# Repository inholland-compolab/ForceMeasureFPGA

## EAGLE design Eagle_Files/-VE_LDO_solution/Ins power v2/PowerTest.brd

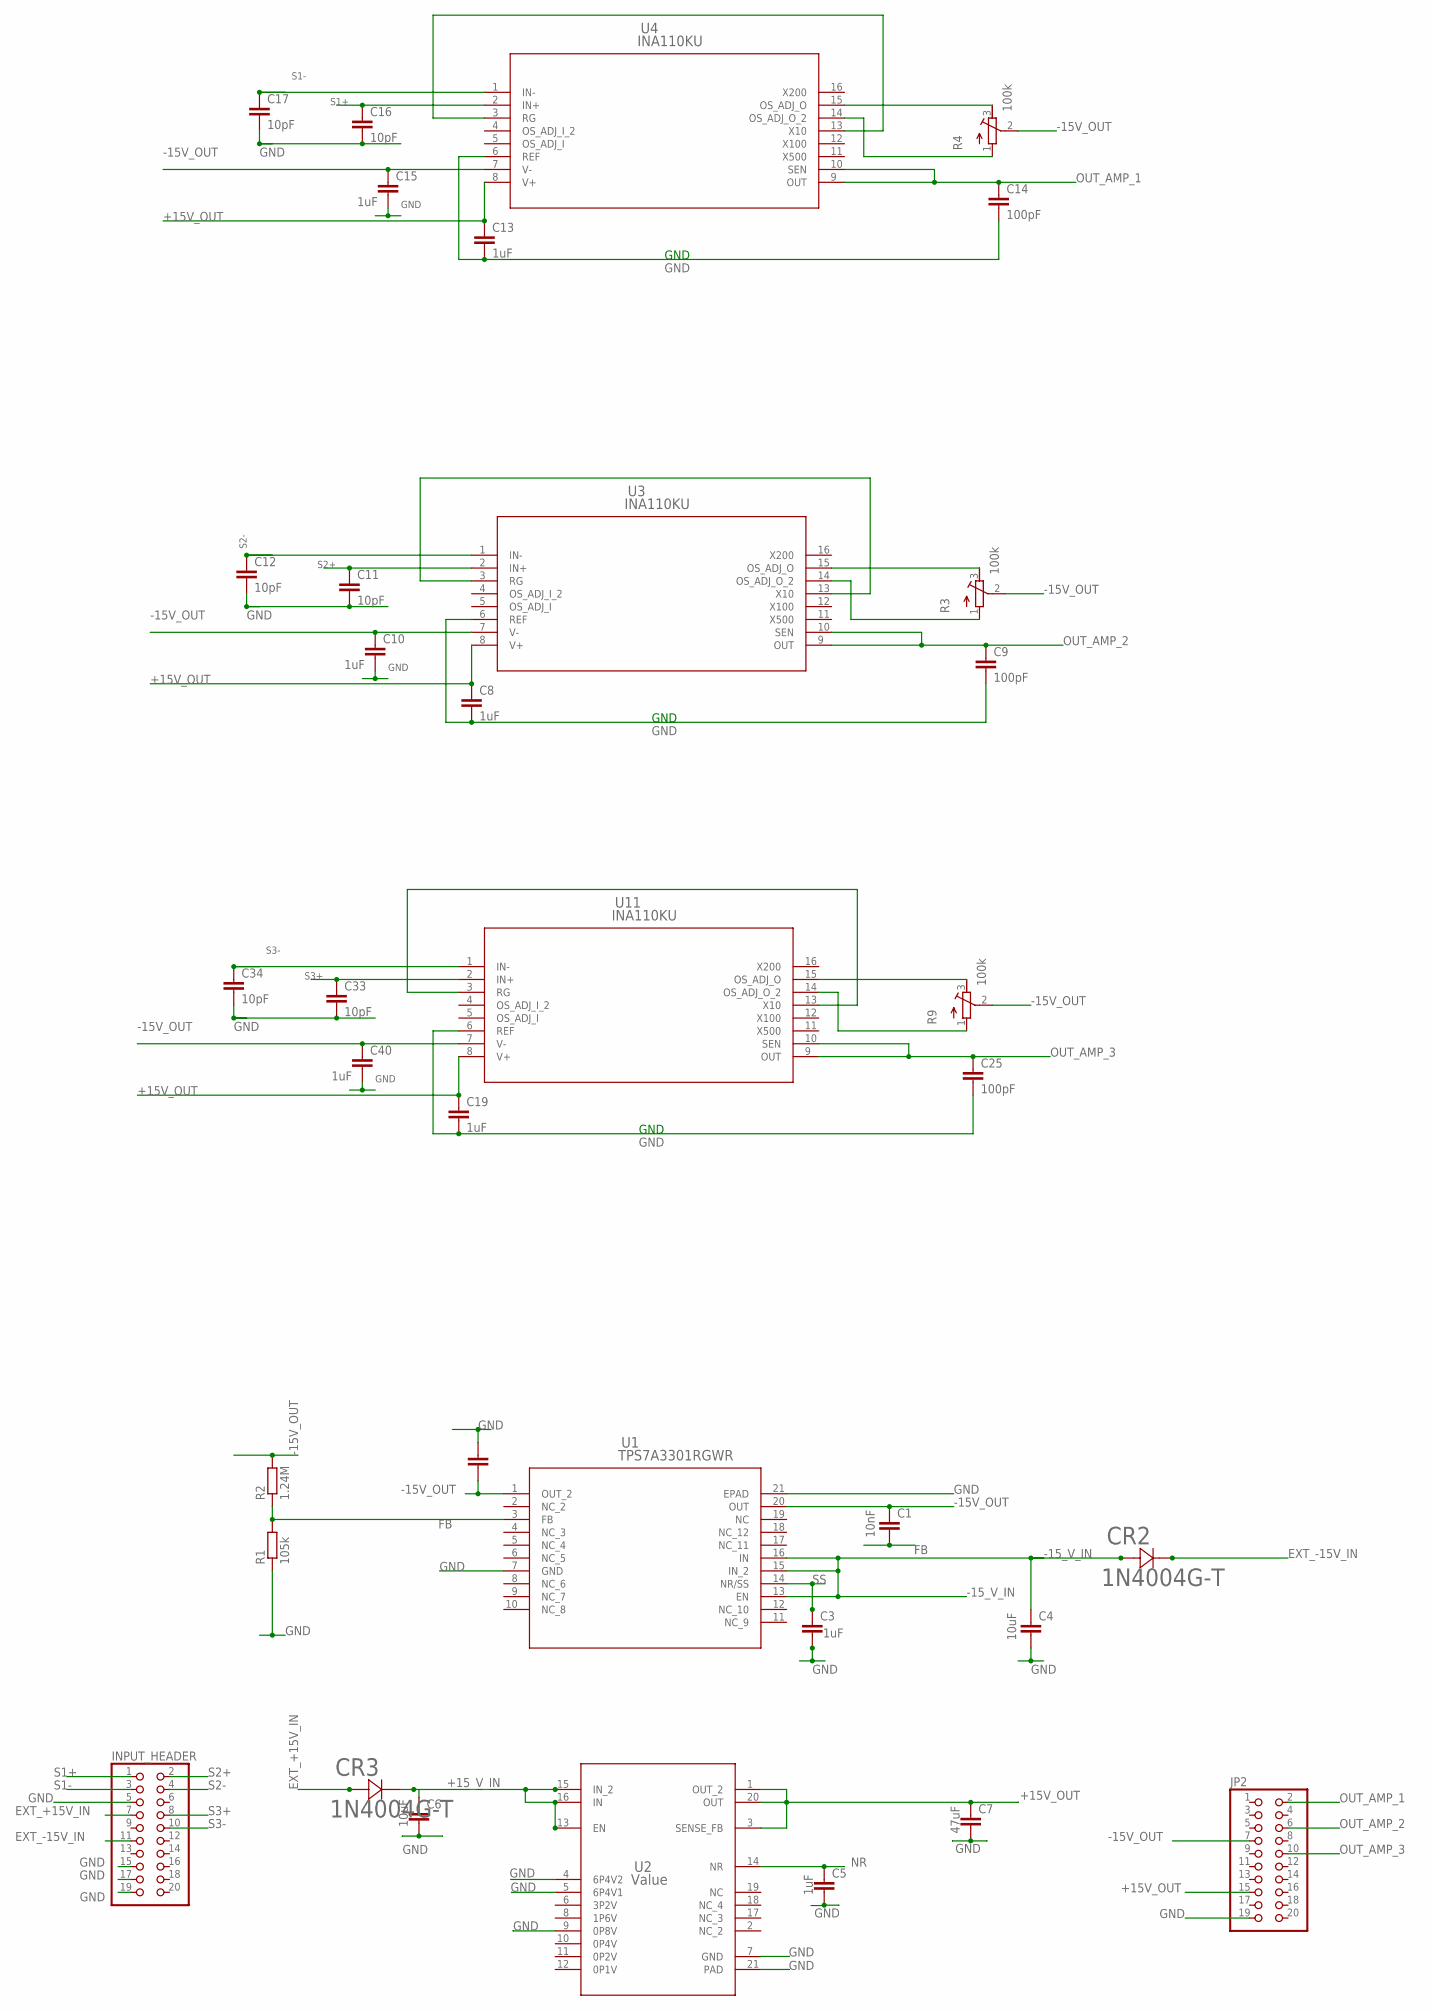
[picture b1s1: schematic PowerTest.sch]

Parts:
C1: 10nF; C1210
C3, C5, C8, C10, C13, C15, C19, C40: 1uF; C1210
C4, C6: 10uF; C1210
C7, C55: 47uF; C1210
C9, C14, C25: 100pF; C1210
C11, C12, C16, C17, C33, C34: 10pF; C1210
CR2, CR3: 1N4004G-T; DO-41
INPUT_HEADER: PINHD-2X10; 2X10
JP2: PINHD-2X10; 2X10
R1: 105k; RESC2012X65
R2: 1.24M; RESC2012X65
R3, R4, R9: 100k; RTRIM3296Y
U1: TPS7A3301RGWR; RGW0020A
U2: Value; RGW0020A
U3, U4, U11: INA110KU; SO-G16G6.9

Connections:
+15V_OUT: C7.1, C8.1, C13.1, C19.1, JP2.15, U2.1 (OUT_2), U2.3 (SENSE_FB), U2.20 (OUT), U3.8 (V+), U4.8 (V+), U11.8 (V+)
+15_V_IN: C6.1, CR3.1, U2.13 (EN), U2.15 (IN_2), U2.16 (IN)
-15V_OUT: C1.1, C10.1, C15.1, C40.1, C55.2, JP2.7, R2.2, R3.2 (S), R4.2 (S), R9.2 (S), U1.1 (OUT_2), U1.20 (OUT), U3.7 (V-), U4.7 (V-), U11.7 (V-)
-15_V_IN: C4.1, CR2.2, U1.13 (EN), U1.15 (IN_2), U1.16 (IN)
EXT_+15V_IN: CR3.2, INPUT_HEADER.7
EXT_-15V_IN: CR2.1, INPUT_HEADER.11
FB: C1.2, R1.2, R2.1, U1.3 (FB)
GND: C3.2, C4.2, C5.2, C6.2, C7.2, C8.2, C9.2, C10.2, C11.2, C12.2, C13.2, C14.2, C15.2, C16.2, C17.2, C19.2, C25.2, C33.2, C34.2, C40.2, C55.1, INPUT_HEADER.5, INPUT_HEADER.15, INPUT_HEADER.17, INPUT_HEADER.19, JP2.19, R1.1, U1.7 (GND), U1.21 (EPAD), U2.4 (6P4V2), U2.5 (6P4V1), U2.7 (GND), U2.9 (0P8V), U2.21 (PAD), U3.6 (REF), U4.6 (REF), U11.6 (REF)
unnamed: U3.3 (RG), U3.13 (X10)
unnamed: U11.3 (RG), U11.13 (X10)
unnamed: R3.3 (E), U3.15 (OS_ADJ_O)
unnamed: R3.1 (A), U3.14 (OS_ADJ_O_2)
unnamed: U4.3 (RG), U4.13 (X10)
unnamed: R4.3 (E), U4.15 (OS_ADJ_O)
unnamed: R4.1 (A), U4.14 (OS_ADJ_O_2)
unnamed: R9.3 (E), U11.15 (OS_ADJ_O)
unnamed: R9.1 (A), U11.14 (OS_ADJ_O_2)
NR: C5.1, U2.14 (NR)
OUT_AMP_1: C14.1, JP2.2, U4.9 (OUT), U4.10 (SEN)
OUT_AMP_2: C9.1, JP2.6, U3.9 (OUT), U3.10 (SEN)
OUT_AMP_3: C25.1, JP2.10, U11.9 (OUT), U11.10 (SEN)
S1+: C16.1, INPUT_HEADER.1, U4.2 (IN+)
S1-: C17.1, INPUT_HEADER.3, U4.1 (IN-)
S2+: C11.1, INPUT_HEADER.2, U3.2 (IN+)
S2-: C12.1, INPUT_HEADER.4, U3.1 (IN-)
S3+: C33.1, INPUT_HEADER.8, U11.2 (IN+)
S3-: C34.1, INPUT_HEADER.10, U11.1 (IN-)
SS: C3.1, U1.14 (NR/SS)

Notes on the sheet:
GND

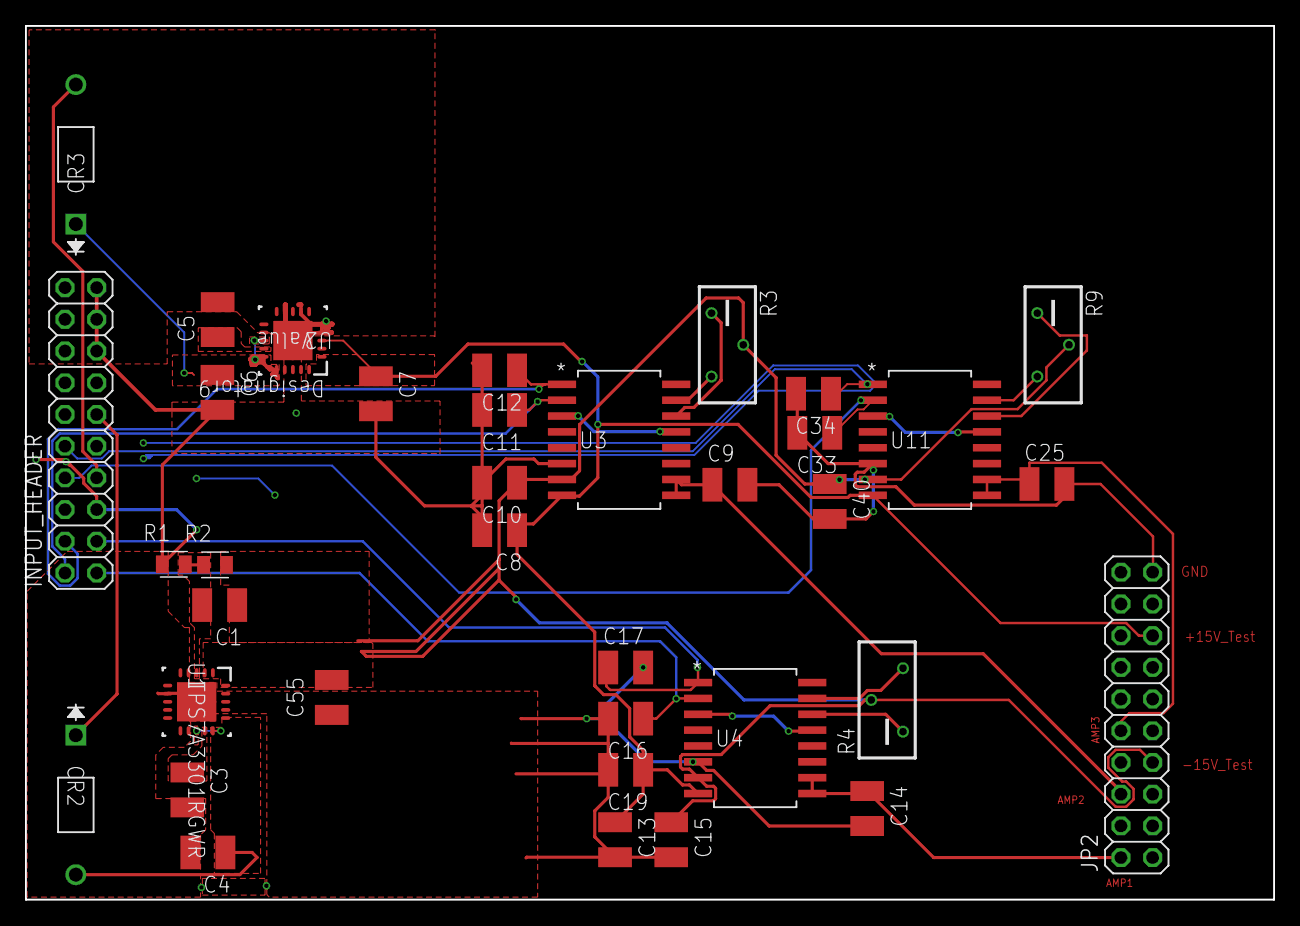
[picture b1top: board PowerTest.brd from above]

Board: 2 copper layers, 100.0 x 70.0 mm, 36 parts (0 on the bottom side), 28 nets.

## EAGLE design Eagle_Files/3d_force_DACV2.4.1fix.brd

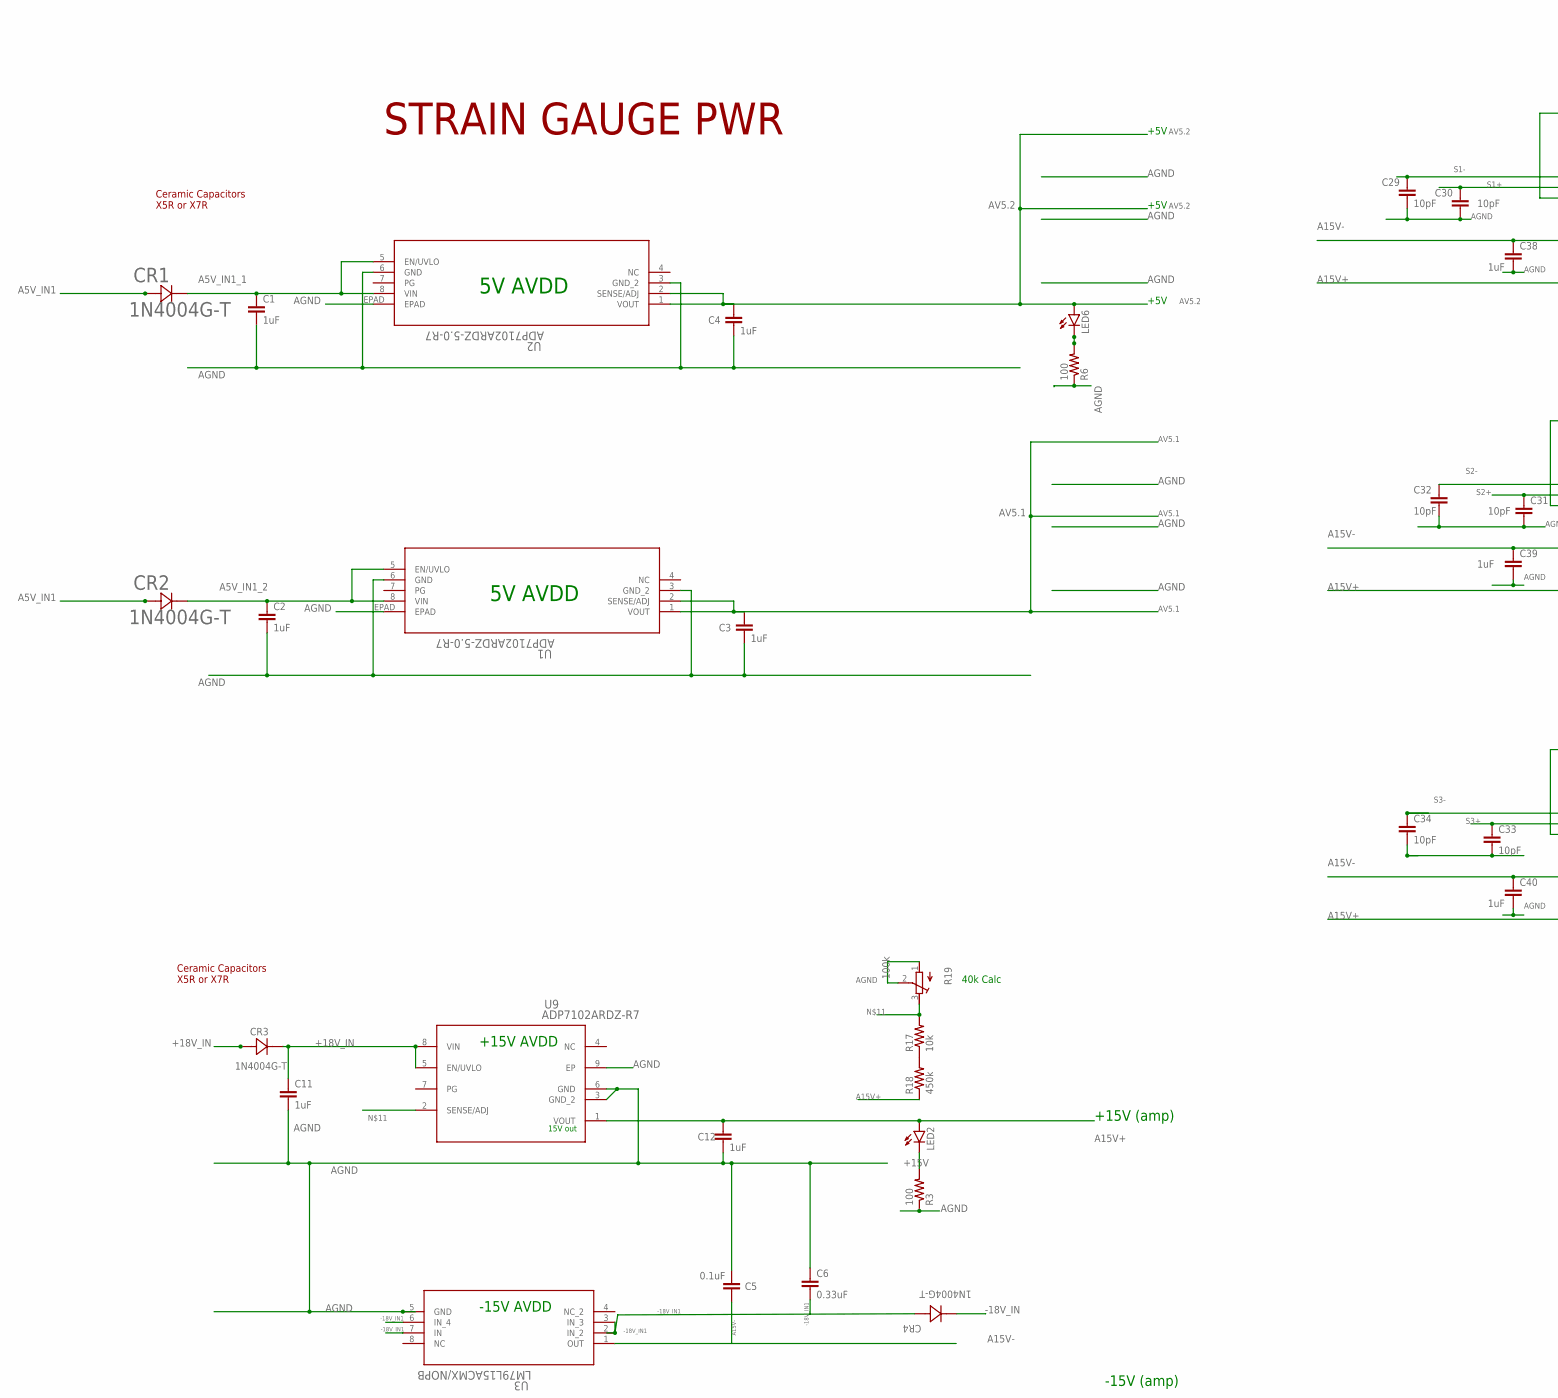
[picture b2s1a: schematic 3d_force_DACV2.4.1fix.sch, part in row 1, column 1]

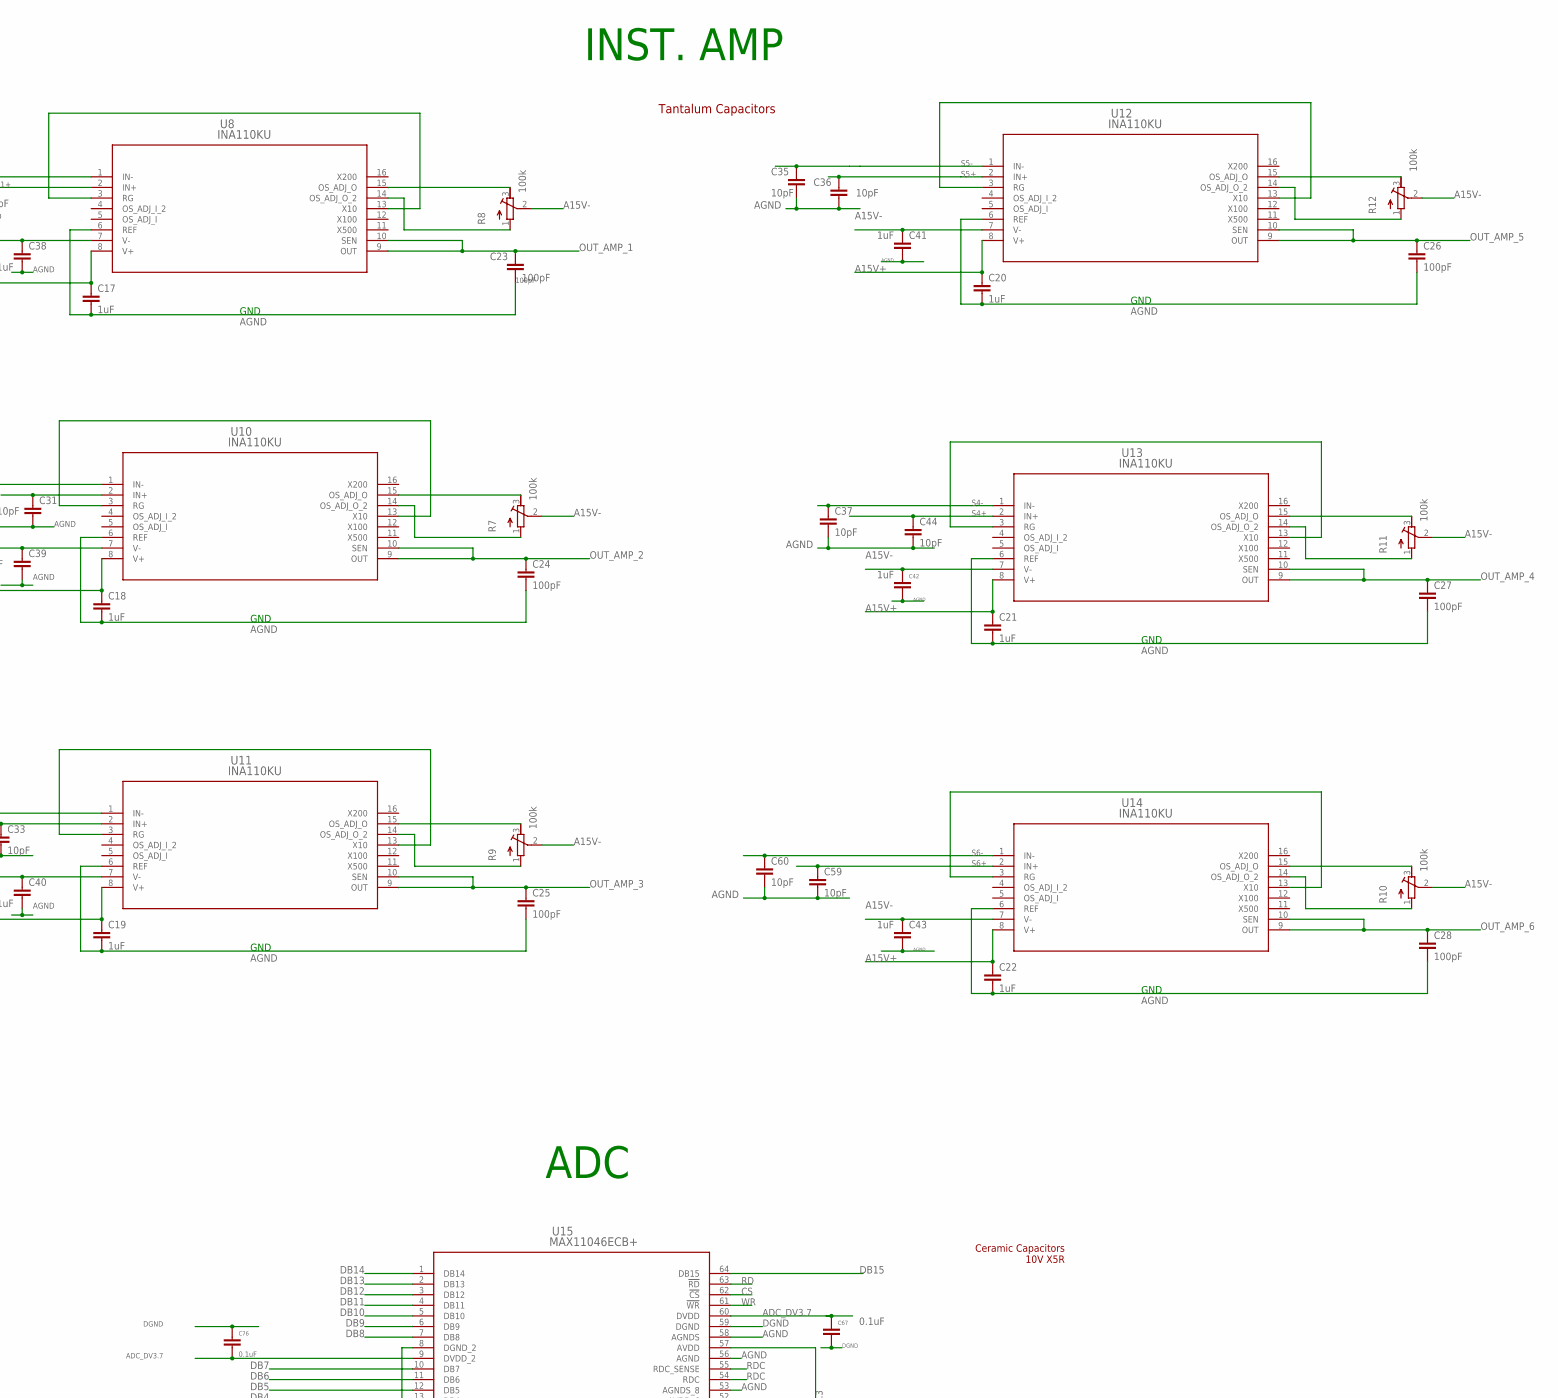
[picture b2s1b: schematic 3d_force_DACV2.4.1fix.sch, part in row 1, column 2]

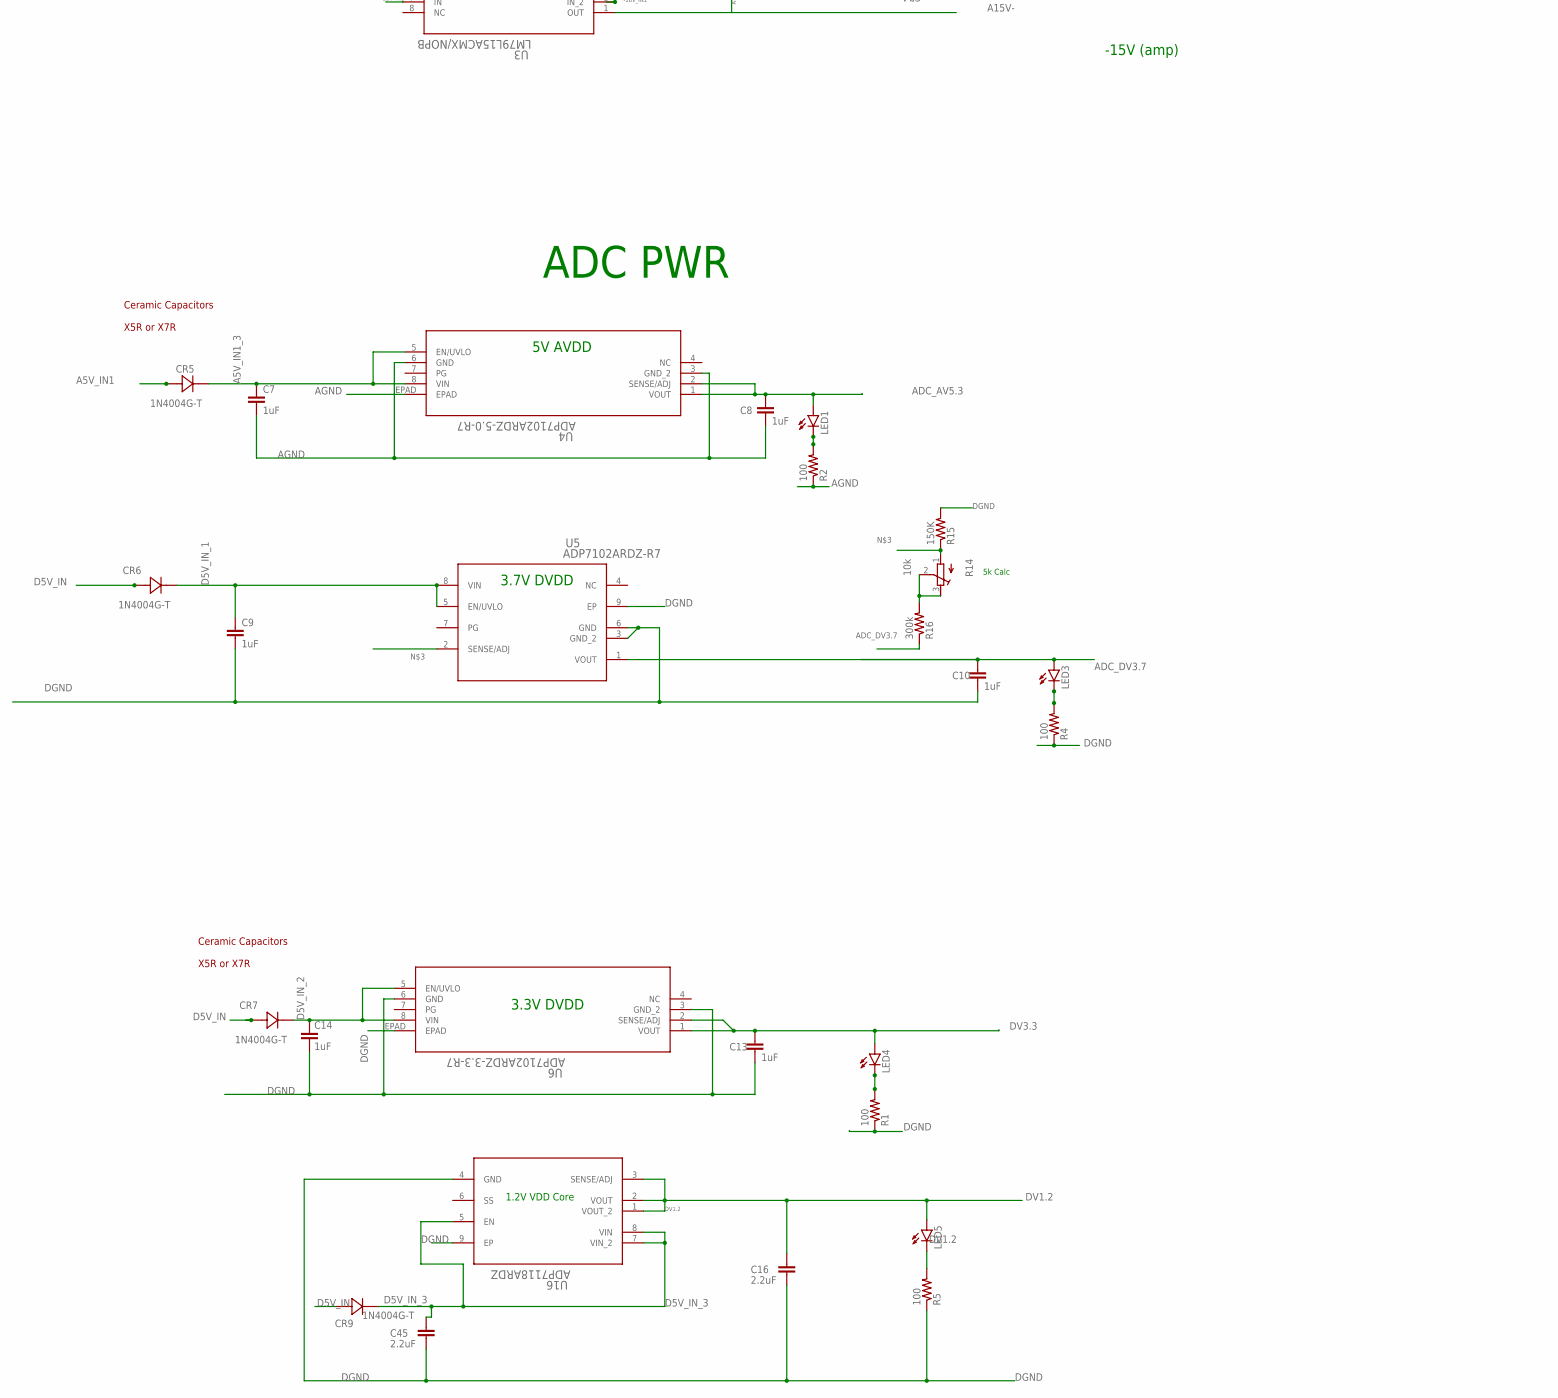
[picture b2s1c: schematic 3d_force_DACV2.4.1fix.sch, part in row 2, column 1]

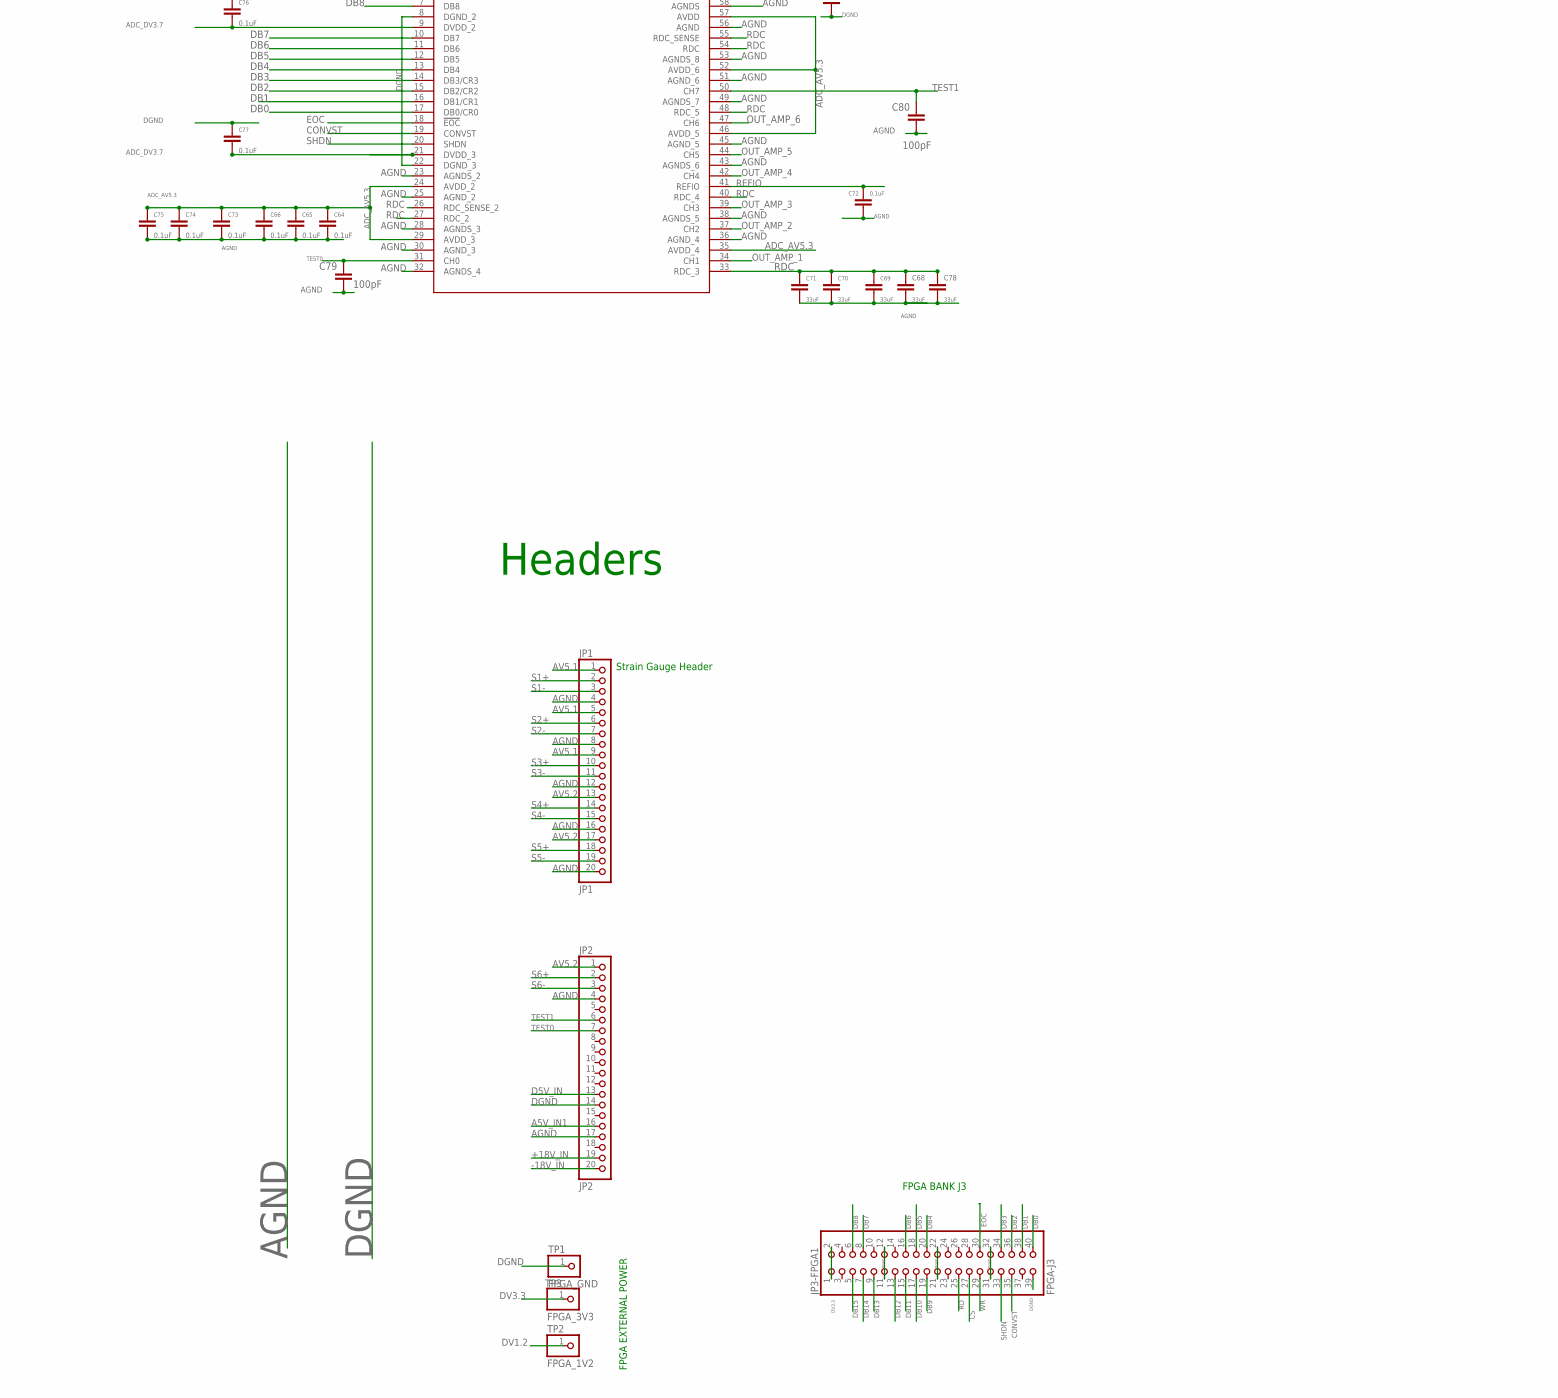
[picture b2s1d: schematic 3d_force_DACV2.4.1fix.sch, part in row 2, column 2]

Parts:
C1, C2, C3, C4, C7, C8, C9, C10, C11, C12, C13, C14, C17, C18, C19, C20, C21, C22, C38, C39, C40, C41, C42, C43: 1uF; C1210
C5, C64, C65, C66, C67, C72, C73, C74, C75, C76, C77: 0.1uF; C1210
C6: 0.33uF; C1210
C16, C45: 2.2uF; C1210
C23, C24, C25, C26, C27, C28, C79, C80: 100pF; C1210
C29, C30, C31, C32, C33, C34, C35, C36, C37, C44, C59, C60: 10pF; C1210
C68, C69, C70, C71, C78: 33uF; C1210
CR1, CR2, CR3, CR4, CR5, CR6, CR7, CR9: 1N4004G-T; DO-41
JP1: JP1; 1X20
JP2: JP2; 1X20
JP3-FPGA1: FPGA-J3; 2X20
LED1, LED2, LED3, LED4, LED5, LED6: LEDCHIPLED_1206; CHIPLED_1206
R1, R2, R3, R4, R5, R6: 100; R0805
R7, R8, R9, R10, R11, R12, R19: 100k; RTRIM3296Y
R14: 10k; RTRIM3296Y
R15: 150K; R1210
R16: 300k; R1210
R17: 10k; R1210
R18: 450k; R1210
TP1: FPGA_GND; 1X01
TP2: FPGA_1V2; 1X01
TP3: FPGA_3V3; 1X01
U1, U2, U4: ADP7102ARDZ-5.0-R7; RD_8_2
U3: LM79L15ACMX/NOPB; M08A
U5, U9: ADP7102ARDZ-R7; RD_8_2
U6: ADP7102ARDZ-3.3-R7; RD_8_2
U8, U10, U11, U12, U13, U14: INA110KU; SO-G16G6.9
U15: MAX11046ECB+; 21-0084C
U16: ADP7118ARDZ; RD_8_1

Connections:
+15V: LED2.C, R3.2
+18V_IN: C11.1, CR3.1, CR3.2, JP2.19, U9.5 (EN/UVLO), U9.8 (VIN)
-18V_IN: CR4.1, JP2.20
-18V_IN1: C6.2, CR4.2, U3.2 (IN_2), U3.3 (IN_3), U3.6 (IN_4), U3.7 (IN)
A5V_IN1: CR1.2, CR2.2, CR5.2, JP2.16
A5V_IN1_1: C1.1, CR1.1, U2.5 (EN/UVLO), U2.8 (VIN)
A5V_IN1_2: C2.1, CR2.1, U1.5 (EN/UVLO), U1.8 (VIN)
A5V_IN1_3: C7.1, CR5.1, U4.5 (EN/UVLO), U4.8 (VIN)
A15V+: C12.1, C17.1, C18.1, C19.1, C20.1, C21.1, C22.1, LED2.A, R18.1, U8.8 (V+), U9.1 (VOUT), U10.8 (V+), U11.8 (V+), U12.8 (V+), U13.8 (V+), U14.8 (V+)
A15V-: C5.1, C38.1, C39.1, C40.1, C41.1, C42.1, C43.1, R7.2 (S), R8.2 (S), R9.2 (S), R10.2 (S), R11.2 (S), R12.2 (S), U3.1 (OUT), U8.7 (V-), U10.7 (V-), U11.7 (V-), U12.7 (V-), U13.7 (V-), U14.7 (V-)
ADC_AV5.3: C8.1, C64.1, C65.1, C66.1, C73.1, C74.1, C75.1, LED1.A, LED1.C, R2.2, U4.1 (VOUT), U4.2 (SENSE/ADJ), U15.24 (AVDD_2), U15.29 (AVDD_3), U15.35 (AVDD_4), U15.46 (AVDD_5), U15.52 (AVDD_6), U15.57 (AVDD)
ADC_DV3.7: C10.1, C67.1, C76.2, C77.2, LED3.A, LED3.C, R4.2, R16.1, U5.1 (VOUT), U15.9 (DVDD_2), U15.21 (DVDD_3), U15.60 (DVDD)
AGND: C1.2, C2.2, C3.2, C4.2, C5.2, C6.1, C7.2, C8.2, C11.2, C12.2, C17.2, C18.2, C19.2, C20.2, C21.2, C22.2, C23.2, C24.2, C25.2, C26.2, C27.2, C28.2, C29.2, C30.2, C31.2, C32.2, C35.2, C36.2, C37.2, C38.2, C39.2, C40.2, C41.2, C42.2, C43.2, C44.2, C59.2, C60.2, C64.2, C65.2, C66.2, C68.2, C69.2, C70.2, C71.2, C72.2, C73.2, C74.2, C75.2, C78.2, C79.2, C80.2, JP1.4, JP1.8, JP1.12, JP1.16, JP1.20, JP2.4, JP2.17, R2.1, R3.1, R6.1, R19.1 (A), R19.2 (S), U1.3 (GND_2), U1.6 (GND), U1.EPAD, U2.3 (GND_2), U2.6 (GND), U2.EPAD, U3.5 (GND), U4.3 (GND_2), U4.6 (GND), U4.EPAD, U8.6 (REF), U9.3 (GND_2), U9.6 (GND), U9.9 (EP), U10.6 (REF), U11.6 (REF), U12.6 (REF), U13.6 (REF), U14.6 (REF), U15.23 (AGNDS_2), U15.25 (AGND_2), U15.28 (AGNDS_3), U15.30 (AGND_3), U15.32 (AGNDS_4), U15.36 (AGND_4), U15.38 (AGNDS_5), U15.43 (AGNDS_6), U15.45 (AGND_5), U15.49 (AGNDS_7), U15.51 (AGND_6), U15.53 (AGNDS_8), U15.56 (AGND), U15.58 (AGNDS)
AV5.1: C3.1, JP1.1, JP1.5, JP1.9, U1.1 (VOUT), U1.2 (SENSE/ADJ)
AV5.2: C4.1, JP1.13, JP1.17, JP2.1, LED6.A, LED6.C, R6.2, U2.1 (VOUT), U2.2 (SENSE/ADJ)
CONVST: JP3-FPGA1.35, U15.19 (CONVST)
CS: JP3-FPGA1.27, U15.62 (!CS)
D5V_IN: CR6.2, CR7.2, CR9.2, JP2.13
D5V_IN_1: C9.1, CR6.1, U5.5 (EN/UVLO), U5.8 (VIN)
D5V_IN_2: C14.1, CR7.1, U6.5 (EN/UVLO), U6.8 (VIN)
D5V_IN_3: C45.1, CR9.1, U16.5 (EN), U16.7 (VIN_2), U16.8 (VIN)
DB0: JP3-FPGA1.40, U15.17 (DB0/CR0)
DB1: JP3-FPGA1.38, U15.16 (DB1/CR1)
DB2: JP3-FPGA1.36, U15.15 (DB2/CR2)
DB3: JP3-FPGA1.34, U15.14 (DB3/CR3)
DB4: JP3-FPGA1.20, U15.13 (DB4)
DB5: JP3-FPGA1.18, U15.12 (DB5)
DB6: JP3-FPGA1.16, U15.11 (DB6)
DB7: JP3-FPGA1.8, U15.10 (DB7)
DB8: JP3-FPGA1.6, U15.7 (DB8)
DB9: JP3-FPGA1.19, U15.6 (DB9)
DB10: JP3-FPGA1.17, U15.5 (DB10)
DB11: JP3-FPGA1.15, U15.4 (DB11)
DB12: JP3-FPGA1.13, U15.3 (DB12)
DB13: JP3-FPGA1.9, U15.2 (DB13)
DB14: JP3-FPGA1.7, U15.1 (DB14)
DB15: JP3-FPGA1.5, U15.64 (DB15)
DGND: C9.2, C10.2, C13.2, C14.2, C16.2, C45.2, C67.2, C76.1, C77.1, JP2.14, JP3-FPGA1.11, JP3-FPGA1.12, JP3-FPGA1.21, JP3-FPGA1.22, JP3-FPGA1.31, JP3-FPGA1.32, JP3-FPGA1.39, R1.1, R4.1, R5.1, R15.2, TP1.1, U5.3 (GND_2), U5.6 (GND), U5.9 (EP), U6.3 (GND_2), U6.6 (GND), U6.EPAD, U15.8 (DGND_2), U15.22 (DGND_3), U15.59 (DGND), U16.4 (GND), U16.9 (EP)
DV1.2: C16.1, LED5.A, LED5.C, R5.2, TP2.1, U16.1 (VOUT_2), U16.2 (VOUT), U16.3 (SENSE/ADJ)
DV3.3: C13.1, JP3-FPGA1.1, JP3-FPGA1.2, LED4.A, LED4.C, R1.2, TP3.1, U6.1 (VOUT), U6.2 (SENSE/ADJ)
EOC: JP3-FPGA1.30, U15.18 (!EOC)
unnamed: U10.3 (RG), U10.13 (X10)
unnamed: R14.1 (A), R15.1, U5.2 (SENSE/ADJ)
unnamed: U11.3 (RG), U11.13 (X10)
unnamed: U12.3 (RG), U12.13 (X10)
unnamed: U13.3 (RG), U13.13 (X10)
unnamed: U14.3 (RG), U14.13 (X10)
unnamed: R7.3 (E), U10.15 (OS_ADJ_O)
unnamed: R7.1 (A), U10.14 (OS_ADJ_O_2)
unnamed: R8.3 (E), U8.15 (OS_ADJ_O)
unnamed: R17.2, R19.3 (E), U9.2 (SENSE/ADJ)
unnamed: R8.1 (A), U8.14 (OS_ADJ_O_2)
unnamed: R9.3 (E), U11.15 (OS_ADJ_O)
unnamed: R9.1 (A), U11.14 (OS_ADJ_O_2)
unnamed: R10.3 (E), U14.15 (OS_ADJ_O)
unnamed: R10.1 (A), U14.14 (OS_ADJ_O_2)
unnamed: R11.3 (E), U13.15 (OS_ADJ_O)
unnamed: U8.3 (RG), U8.13 (X10)
unnamed: R11.1 (A), U13.14 (OS_ADJ_O_2)
unnamed: R12.3 (E), U12.15 (OS_ADJ_O)
unnamed: R12.1 (A), U12.14 (OS_ADJ_O_2)
unnamed: C33.2, C34.2
unnamed: R14.2 (S), R14.3 (E), R16.2
unnamed: R17.1, R18.2
OUT_AMP_1: C23.1, U8.9 (OUT), U8.10 (SEN), U15.34 (CH1)
OUT_AMP_2: C24.1, U10.9 (OUT), U10.10 (SEN), U15.37 (CH2)
OUT_AMP_3: C25.1, U11.9 (OUT), U11.10 (SEN), U15.39 (CH3)
OUT_AMP_4: C27.1, U13.9 (OUT), U13.10 (SEN), U15.42 (CH4)
OUT_AMP_5: C26.1, U12.9 (OUT), U12.10 (SEN), U15.44 (CH5)
OUT_AMP_6: C28.1, U14.9 (OUT), U14.10 (SEN), U15.47 (CH6)
PG: U1.7 (PG), U2.7 (PG), U4.7 (PG), U6.7 (PG)
RD: JP3-FPGA1.25, U15.63 (!RD)
RDC: C68.1, C69.1, C70.1, C71.1, C78.1, U15.26 (RDC_SENSE_2), U15.27 (RDC_2), U15.33 (RDC_3), U15.40 (RDC_4), U15.48 (RDC_5), U15.54 (RDC), U15.55 (RDC_SENSE)
REFIO: C72.1, U15.41 (REFIO)
S1+: C30.1, JP1.2, U8.2 (IN+)
S1-: C29.1, JP1.3, U8.1 (IN-)
S2+: C31.1, JP1.6, U10.2 (IN+)
S2-: C32.1, JP1.7, U10.1 (IN-)
S3+: C33.1, JP1.10, U11.2 (IN+)
S3-: C34.1, JP1.11, U11.1 (IN-)
S4+: C44.1, JP1.14, U13.2 (IN+)
S4-: C37.1, JP1.15, U13.1 (IN-)
S5+: C36.1, JP1.18, U12.2 (IN+)
S5-: C35.1, JP1.19, U12.1 (IN-)
S6+: C59.1, JP2.2, U14.2 (IN+)
S6-: C60.1, JP2.3, U14.1 (IN-)
SHDN: JP3-FPGA1.33, U15.20 (SHDN)
TEST0: C79.1, JP2.7, U15.31 (CH0)
TEST1: C80.1, JP2.6, U15.50 (CH7)
WR: JP3-FPGA1.29, U15.61 (!WR)

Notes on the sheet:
5V AVDD
+5V
+15V AVDD
+15V (amp)
-15V AVDD
-15V (amp)
ADC PWR
STRAIN GAUGE PWR
3.7V DVDD
3.3V DVDD
GND
INST. AMP
1.2V VDD Core
FPGA EXTERNAL POWER
Strain Gauge Header
Headers
15V out
Tantalum Capacitors
Ceramic Capacitors X5R or X7R
Ceramic Capacitors X5R or X7R
Ceramic Capacitors X5R or X7R
40k Calc
5k Calc
FPGA BANK J3
ADC
Ceramic Capacitors 10V X5R

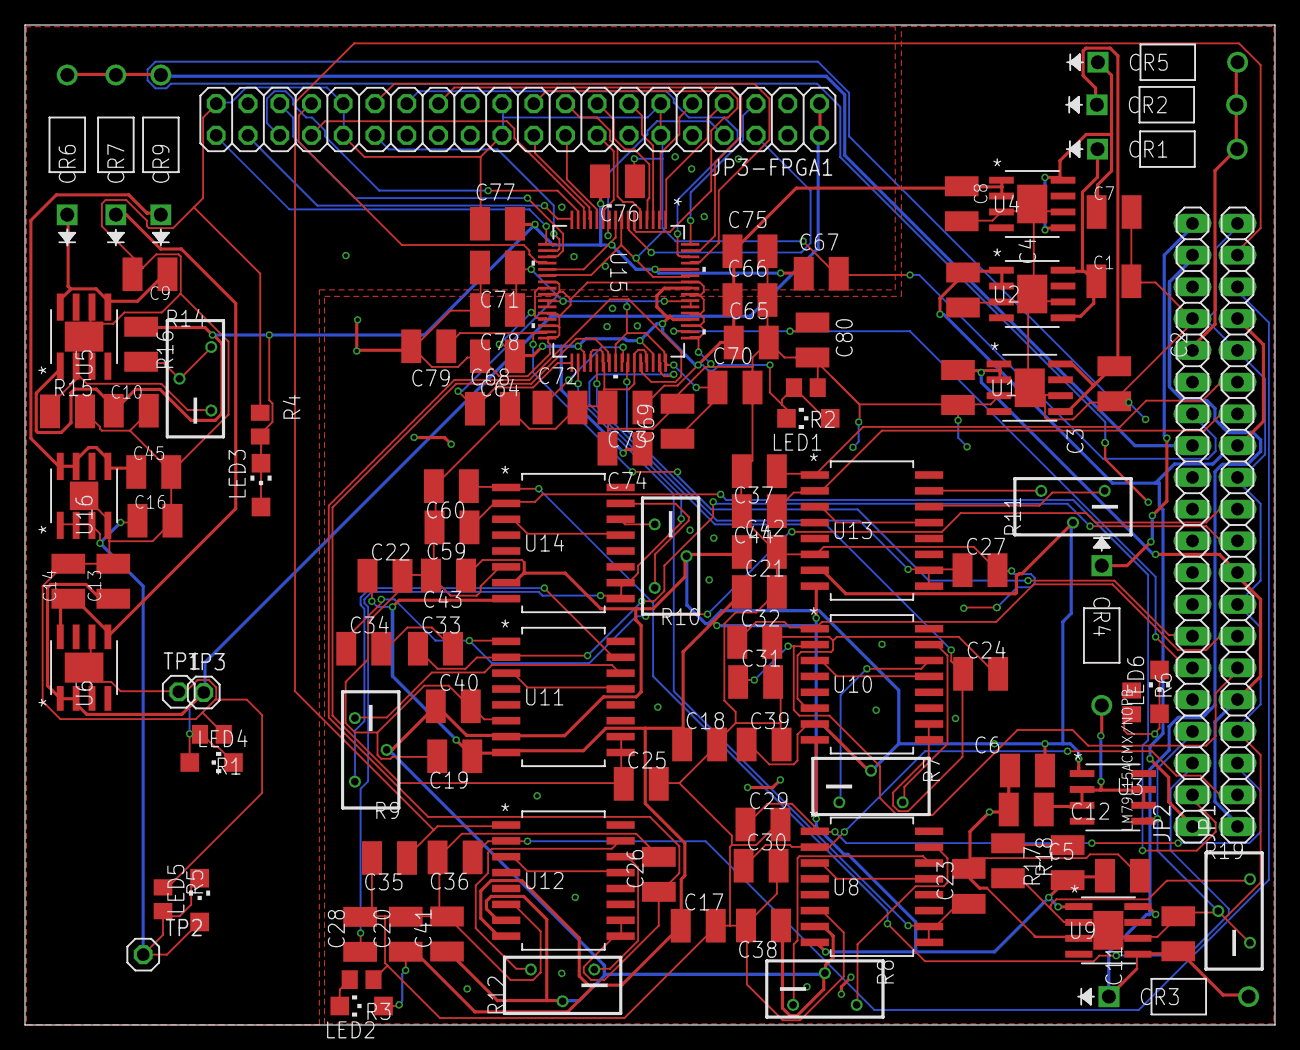
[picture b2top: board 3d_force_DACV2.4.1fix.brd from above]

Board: 2 copper layers, 100.0 x 80.0 mm, 116 parts (0 on the bottom side), 90 nets.

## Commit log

2020-07-10 Revert "Create Timing_diagram_draft.pdf"
    This reverts commit eacb4d3757d5c717b0305247a8c0592ec4bb1ce2.
2020-07-10 Revert "Revert "Create Timing_diagram_draft.pdf""
    This reverts commit 938052372199a50549879828df8948a30088d4e9.
2020-07-10 Eagle files added
2020-07-10 verilog codes
2020-07-21 Create BOM_INSPWR_TEST.pdf
    BOM
2020-08-25 Create Force measurement road map.docx
    .
